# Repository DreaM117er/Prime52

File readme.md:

# Prime52 v1

- 中文說明（Chinese Readme）。
- [英文說明（English Readme）](readme_en.md)。

|||
|--|--|
|||

## 詳細說明

一直到現在為止，我還是無法適應軌跡球...

我個人沒有辦法去適應軌跡球的移動模式，更不用說要用什麼方式去操作它，因此在我將探索者1號設計出來的當下，我就知道還有一個將遊戲搖桿（Joystick）加進鍵盤內的構想在，也確實也有不少前輩設計出來，比如Dactyl Manuform Skeleton Edition的完整STL模型中，就有搖桿的存在。但礙於當時的我沒有足夠地了解3D建模及QMK韌體，一直到現在才有能力將這個很久以前就一直深埋在內心的夢想付諸實行。

它叫做Prime52，很簡單直接地說，它就是搭載Joy-con搖桿、EC-11旋轉編碼器及滑鼠滾輪的一把矮軸鍵盤，支援Choc v1、v2熱插拔。

## 使用材料

|名稱|數量|備註|連結|
|--|--|--|--|
|PCB|1|左、右|-|
|FR4外殼|2|含擋板|-|
|`RP2040Supermini`|2|-|[Link](https://www.aliexpress.com/item/1005006096780891.html?channel=twinner)|
|`EC-11`旋鈕編碼器|2|高`15mm`|[Link](https://www.aliexpress.com/item/1005006104167148.html?channel=twinner)| 
|`EC-11`編碼器帽蓋|2|`可選配`，有提供3D模型|-|
|`EC10E`滑鼠編碼器|2|高`11mm`|[Link](https://www.aliexpress.com/item/1005006279296138.html?channel=twinner)|
|`MR-0017`滑鼠滾輪|2|`可選配`，有提供3D模型|[Link](https://www.aliexpress.com/item/1005005878223914.html?channel=twinner)|
|`Joy-con`搖桿|2|`6pin`直插式|[Link](https://vi.aliexpress.com/item/1005006061159473.html)|
|`3.5mm` TRRS座|2|`4Pin`直插式|[Link](https://vi.aliexpress.com/item/1005003299392377.html?channel=twinner)|
|M2x`4mm` 雙通銅柱|12|定位板用|-|
|M2x`6mm` 雙通銅柱|6|搖桿用|-|
|M2x`7mm` 雙通銅柱|10|擋板用|-|
|M2x`15mm` 雙通銅柱|4|滑鼠滾輪用|-|
|M2x`3mm` 扁頭螺絲|48|-|-|
|M2x`8mm` 扁頭螺絲|16|-|-|
|`M2` 螺母|16|-|-|
|`M2` 防滑墊片|16||-|
|`ø8x1.5mm` 自黏腳貼|-|-|-|
|滑鼠用`微動開關`|2|-|[Link](https://vi.aliexpress.com/w/wholesale-mouse-switch.html?spm=a2g0o.productlist.search.0)|
|二極體 `1N4148`|52|貼片式 `SOD-123`|-|
|凱華`Choc`規格鍵軸|46|支援v1、v2|-|
|凱華`Choc`系列熱插拔座|46|-|[Link](https://vi.aliexpress.com/item/1005003879769486.html?channel=twinner)|
|`SK6212Mini-E` 反向LED燈|46|`選配`|[Link](https://vi.aliexpress.com/item/1005005956813491.html?channel=twinner)|

> **Note**
>
> 組裝鍵盤前務必先將韌體刷入MCU中，便測試及安裝方面會比較輕鬆容易：[點我進入組裝說明](guide.md)

## 現階段版本問題點

|||
|--|--|
|||

- 滑鼠滾輪安裝上的困難，未來改進有無按鍵雙支援。
- 滑鼠編碼器的脈衝問題（暫時無法解決）。
- MCU的侷限性，未來可以支援更多類型的MCU，往大眾常使用的為主。
- 電路板的走線問題，也是無法支援更多MCU的主因。
- Slave端搖桿電位漂移、LED燈訊號有時而不穩定，有可能會開發新的鍵盤直接改掉這些問題。
- 看似對稱，但無法設計成對稱（Joy-con搖桿的主因）。

這是實際到手的`v1`版本在組裝上遇到的問題，`v2`版本的PCB會解決這個問題，並且會開發`MX`及`GLP`的版本出來。

## 使用資源

- Datasheets from TTC, ALPS, Huano.
- [QMK Firmware](https://qmk.fm/).
- [VIAL](https://get.vial.today/).
- [KiCAD](https://www.kicad.org/) version `7.0.5.`
- [JLCPCB](https://jlcpcb.com/).
- [DeepL](https://www.deepl.com/translator).
- [AutoDesk Fusion](https://www.autodesk.com/products/fusion-360/free-trial).

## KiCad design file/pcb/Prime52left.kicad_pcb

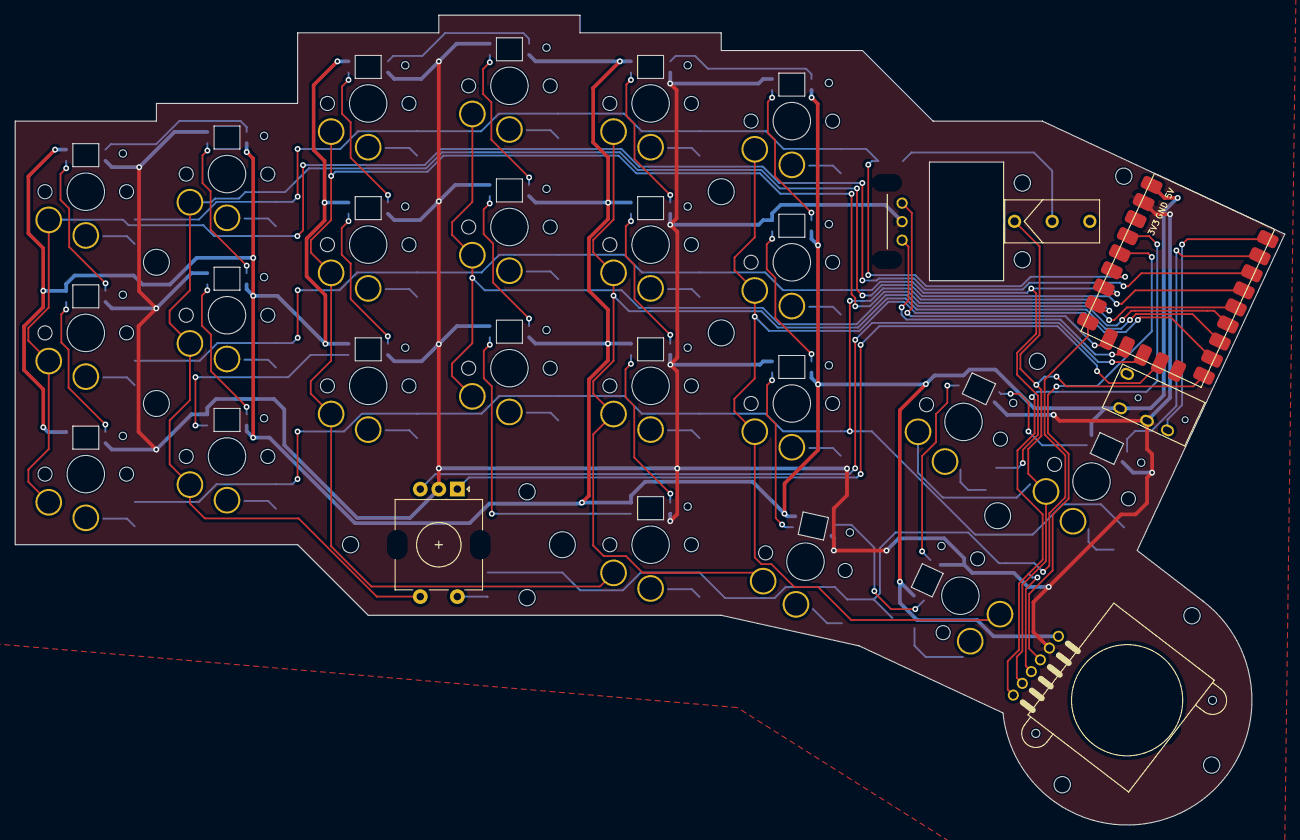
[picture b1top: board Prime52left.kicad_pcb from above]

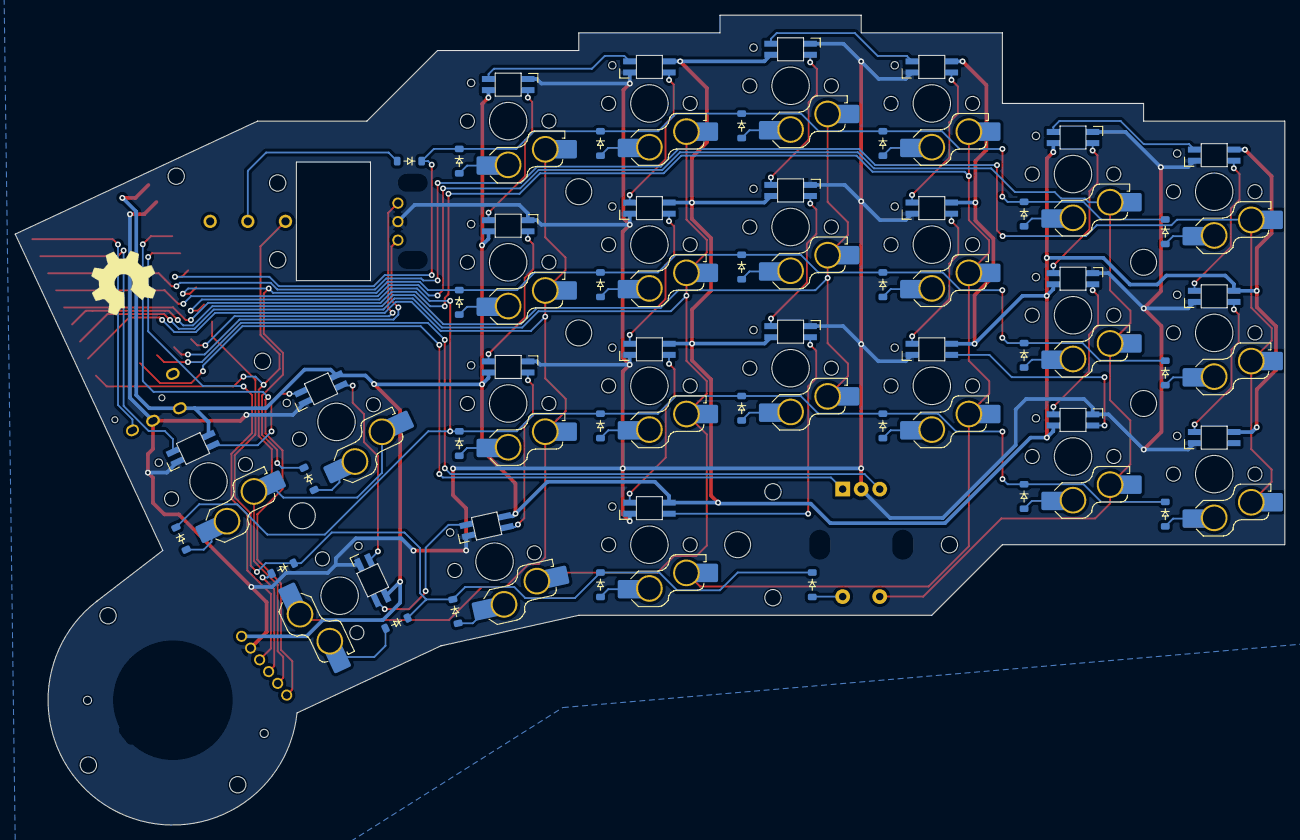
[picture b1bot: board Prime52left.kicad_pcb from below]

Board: 2 copper layers, 171.3 x 109.3 mm, 88 parts (50 on the bottom side), 69 nets.

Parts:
D1, D2, D3, D4, D5, D6, D7, D8, D9, D10, D11, D12, D13, D14, D15, D16, D17, D18, D19, D20, D21, D22, D23, D24, D25, D26: 1N4148_TS; D_SOD-123
H1, H2, H3: M2; MountingHole_2.2mm_M2
H7, H9, H10, H13, H14, H15: 3.5mm; MountingHole_3.5mm
K1, K2, K3, K4, K5, K6, K8, K9, K10, K11, K12, K13, K14, K15, K16, K17, K18, K19, K20, K21, K24, K25: SW_Push; SW_Choc_KLP12_Hotswap_Plated_1.00u
K7: EC-11; RotaryEncoder_EC11
K22: SW_Push; SW_Choc_KLP12_Hotswap_Plated_1.25u
K23: SW_MicroSwitches_Kailh_THT
K26: NS Joy-con; Joystick_NSJoy-con
L1, L2, L3, L4, L5, L6, L7, L8, L9, L10, L11, L12, L13, L14, L15, L16, L17, L18, L19, L20, L21, L22, L23: WS2812B; LED_SK6812MINI-E
RE1: MW; RotaryEncoder_MouseWheel
SYM1: Logo; OSHW-Symbol_8.9x8mm_SilkScreen
T1: TRRS_L; TRRS-PJ-320A
U1: MCU_Left; MCU_RP2040SuperMini_SMD

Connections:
5V-L: K26.6 (VCC), L1.1 (VDD), L2.1 (VDD), L3.1 (VDD), L4.1 (VDD), L5.1 (VDD), L6.1 (VDD), L7.1 (VDD), L8.1 (VDD), L9.1 (VDD), L10.1 (VDD), L11.1 (VDD), L12.1 (VDD), L13.1 (VDD), L14.1 (VDD), L15.1 (VDD), L16.1 (VDD), L17.1 (VDD), L18.1 (VDD), L19.1 (VDD), L20.1 (VDD), L21.1 (VDD), L22.1 (VDD), L23.1 (VDD), T1.1 (T/VCC), U1.1 (5V)
A1: RE1.A (CLK), U1.23 (GP13)
A2: K7.B (DT), U1.21 (GP11)
B1: RE1.B (DT), U1.22 (GP12)
B2: K7.A (CLK), U1.20 (GP10)
GND: K7.C (GND), K26.5 (GND), L1.3 (VSS), L2.3 (VSS), L3.3 (VSS), L4.3 (VSS), L5.3 (VSS), L6.3 (VSS), L7.3 (VSS), L8.3 (VSS), L9.3 (VSS), L10.3 (VSS), L11.3 (VSS), L12.3 (VSS), L13.3 (VSS), L14.3 (VSS), L15.3 (VSS), L16.3 (VSS), L17.3 (VSS), L18.3 (VSS), L19.3 (VSS), L20.3 (VSS), L21.3 (VSS), L22.3 (VSS), L23.3 (VSS), RE1.C (GND), T1.3 (R/GND), U1.2 (GND)
Left_data: T1.2 (R/SNL), U1.10 (GP0)
unnamed: D1.2, K1.1
unnamed: D2.2, K2.1
unnamed: D3.2, K3.1
unnamed: D4.2, K4.1
unnamed: D5.2, K5.1
unnamed: D6.2, K6.1
unnamed: D8.2, K8.1
unnamed: D9.2, K9.1
unnamed: D10.2, K10.1
unnamed: D11.2, K11.1
unnamed: D12.2, K12.1
unnamed: D13.2, K13.1
unnamed: D14.2, K14.1
unnamed: D15.2, K15.1
unnamed: D16.2, K16.1
unnamed: D17.2, K17.1
unnamed: D18.2, K18.1
unnamed: D19.2, K19.1
unnamed: D20.2, K20.1
unnamed: D21.2, K21.1
unnamed: D22.2, K22.2
unnamed: D24.2, K24.1
unnamed: D25.2, K25.1
unnamed: D7.2, K7.S2 (SW)
unnamed: D23.2, K23.2 (S2)
unnamed: D26.2, K26.3 (SW)
unnamed: L1.2 (DOUT), L2.4 (DIN)
unnamed: L2.2 (DOUT), L3.4 (DIN)
unnamed: L3.2 (DOUT), L4.4 (DIN)
unnamed: L4.2 (DOUT), L5.4 (DIN)
unnamed: L5.2 (DOUT), L6.4 (DIN)
unnamed: L6.2 (DOUT), L7.4 (DIN)
unnamed: L7.2 (DOUT), L8.4 (DIN)
unnamed: L8.2 (DOUT), L9.4 (DIN)
unnamed: L9.2 (DOUT), L10.4 (DIN)
unnamed: L10.2 (DOUT), L11.4 (DIN)
unnamed: L11.2 (DOUT), L12.4 (DIN)
unnamed: L12.2 (DOUT), L13.4 (DIN)
unnamed: L13.2 (DOUT), L14.4 (DIN)
unnamed: L14.2 (DOUT), L15.4 (DIN)
unnamed: L15.2 (DOUT), L16.4 (DIN)
unnamed: L16.2 (DOUT), L17.4 (DIN)
unnamed: L17.2 (DOUT), L18.4 (DIN)
unnamed: L18.2 (DOUT), L19.4 (DIN)
unnamed: L19.2 (DOUT), L20.4 (DIN)
unnamed: L20.2 (DOUT), L21.4 (DIN)
unnamed: L21.2 (DOUT), L22.4 (DIN)
unnamed: L22.2 (DOUT), L23.4 (DIN)
RGB-L: L1.4 (DIN), U1.11 (GP1)
X1: K26.1 (X/AD1), U1.4 (GP29)
Y1: K26.4 (Y/AD2), U1.5 (GP28)
col0: K1.2, K2.2, K3.2, U1.12 (GP2)
col1: K4.2, K5.2, K6.2, K7.S1 (GND), U1.13 (GP3)
col2: K8.2, K9.2, K10.2, K11.2, U1.14 (GP4)
col3: K12.2, K13.2, K14.2, U1.15 (GP5)
col4: K15.2, K16.2, K17.2, K18.2, U1.16 (GP6)
col5: K19.2, K20.2, K21.2, K22.1, U1.17 (GP7)
col6: K23.1 (S1), K24.2, K25.2, K26.2 (GND), U1.18 (GP8)
row0: D1.1, D4.1, D8.1, D12.1, D15.1, D19.1, D23.1, U1.6 (GP27)
row1: D2.1, D5.1, D9.1, D13.1, D16.1, D20.1, D24.1, U1.7 (GP26)
row2: D3.1, D6.1, D10.1, D14.1, D17.1, D21.1, D25.1, U1.8 (GP15)
row3: D7.1, D11.1, D18.1, D22.1, D26.1, U1.9 (GP14)

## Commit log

2024-04-14 upload all files
2024-04-14 update list
2024-04-14 update en files
2024-04-14 update and fix all files
